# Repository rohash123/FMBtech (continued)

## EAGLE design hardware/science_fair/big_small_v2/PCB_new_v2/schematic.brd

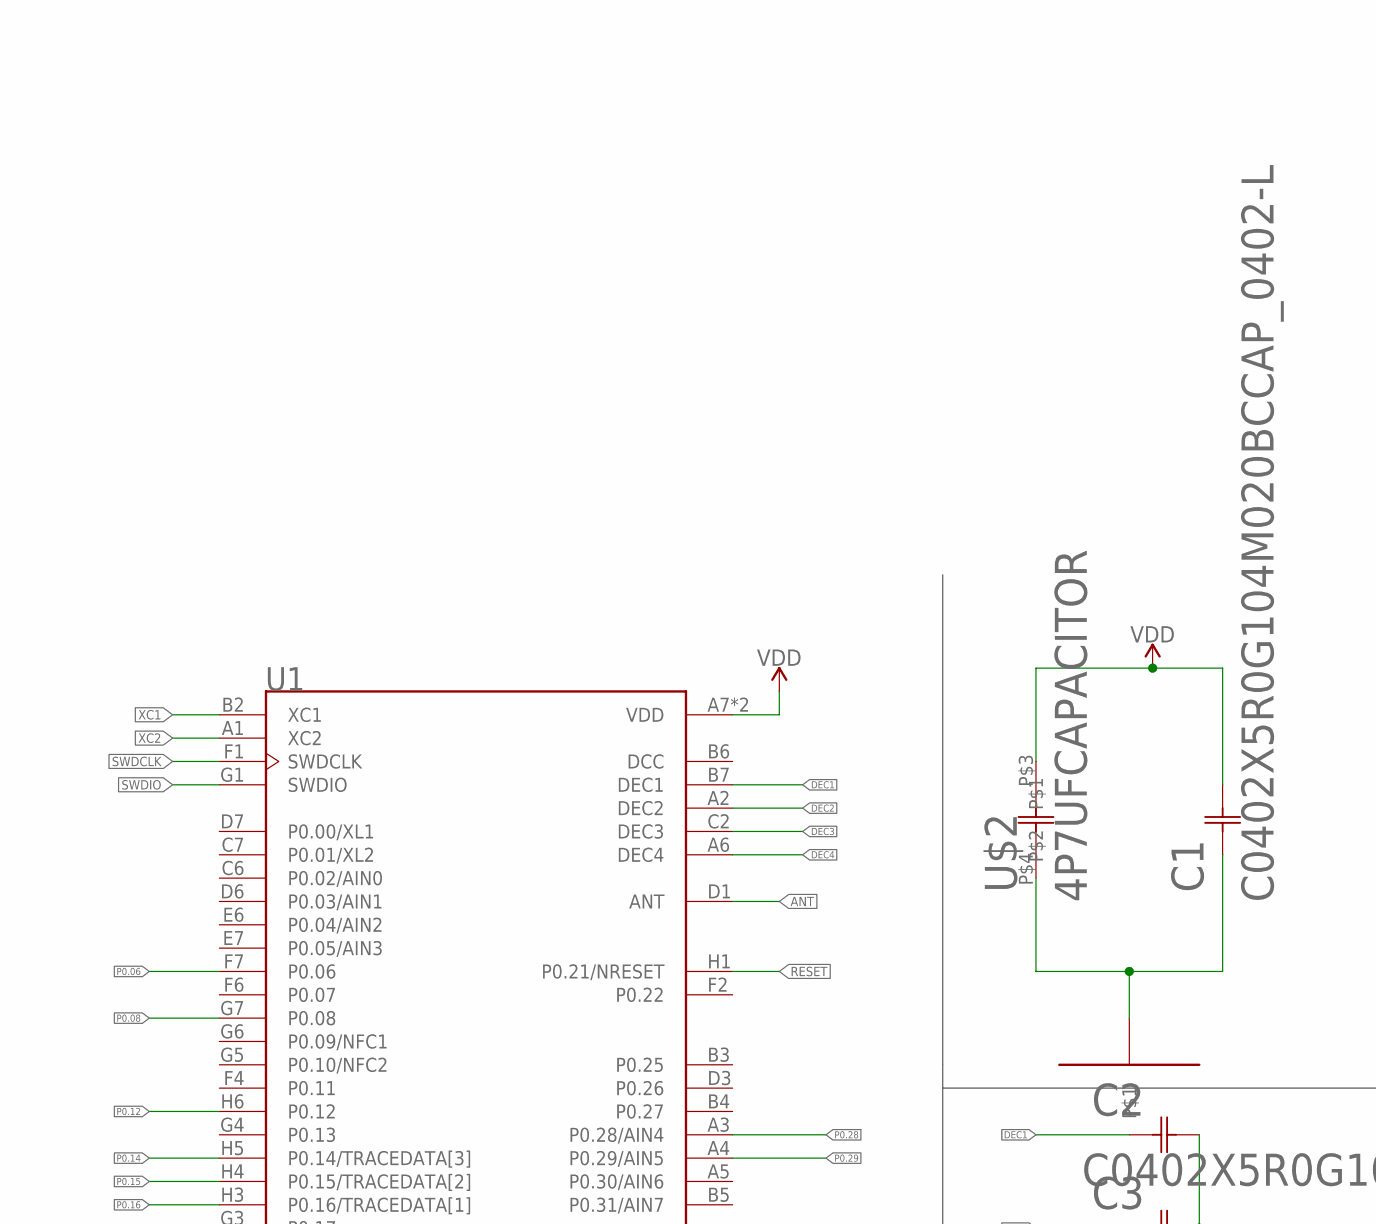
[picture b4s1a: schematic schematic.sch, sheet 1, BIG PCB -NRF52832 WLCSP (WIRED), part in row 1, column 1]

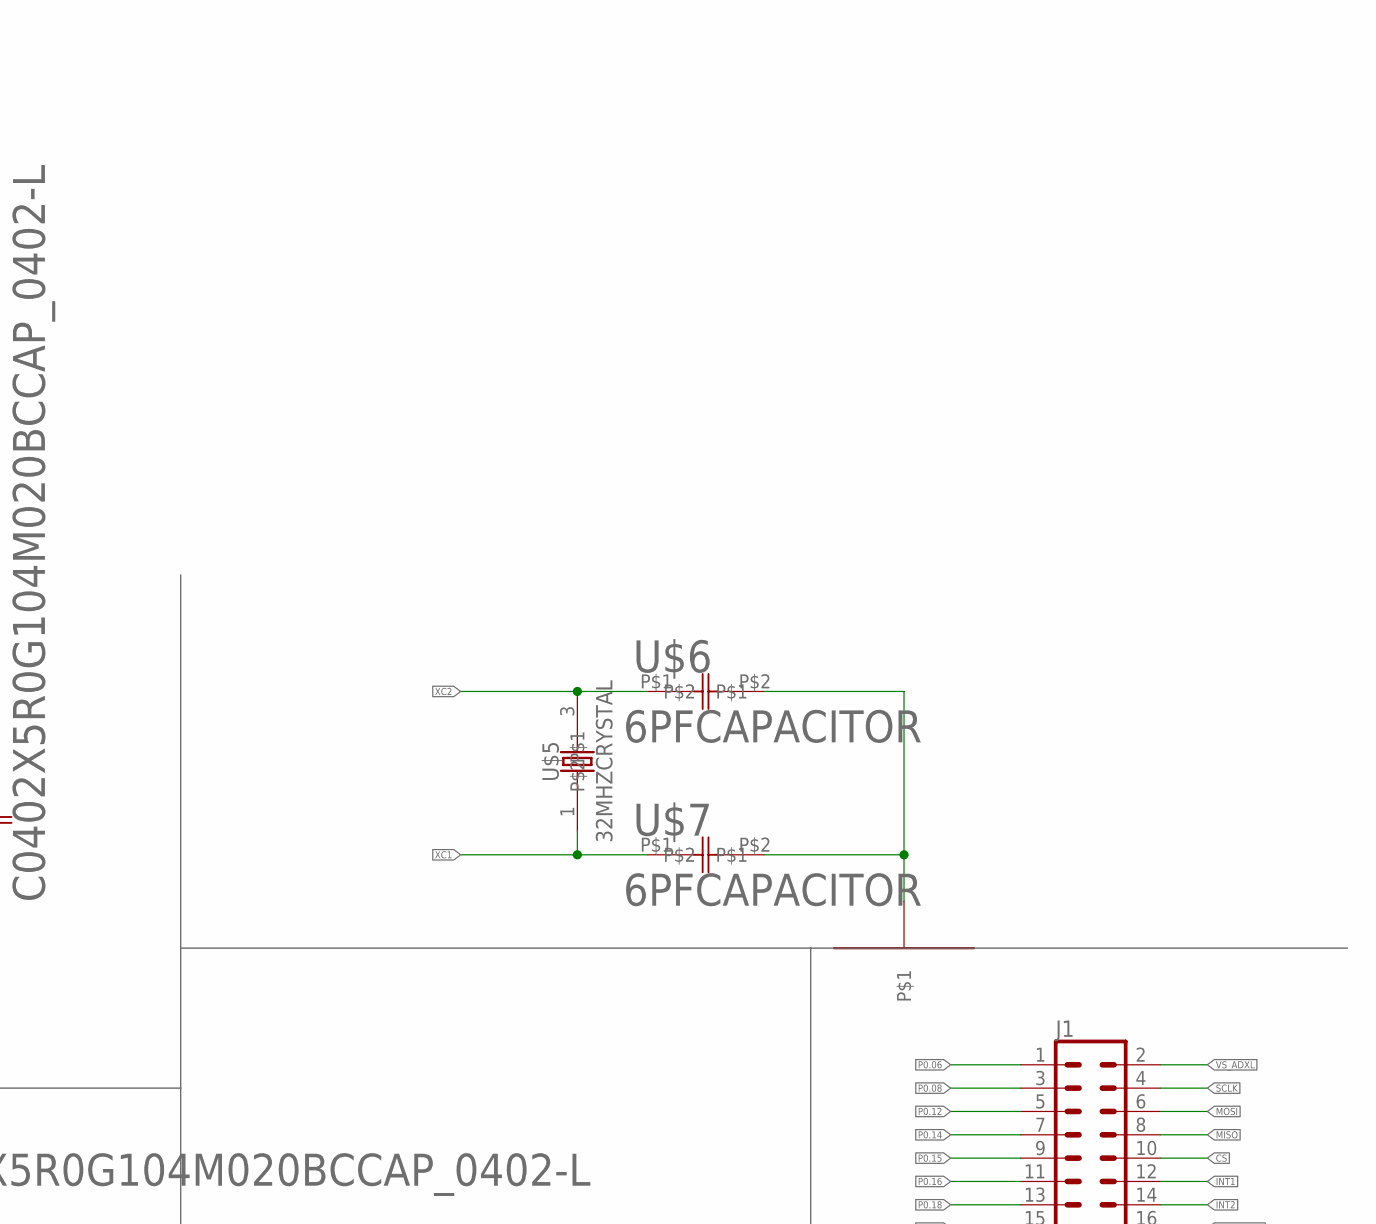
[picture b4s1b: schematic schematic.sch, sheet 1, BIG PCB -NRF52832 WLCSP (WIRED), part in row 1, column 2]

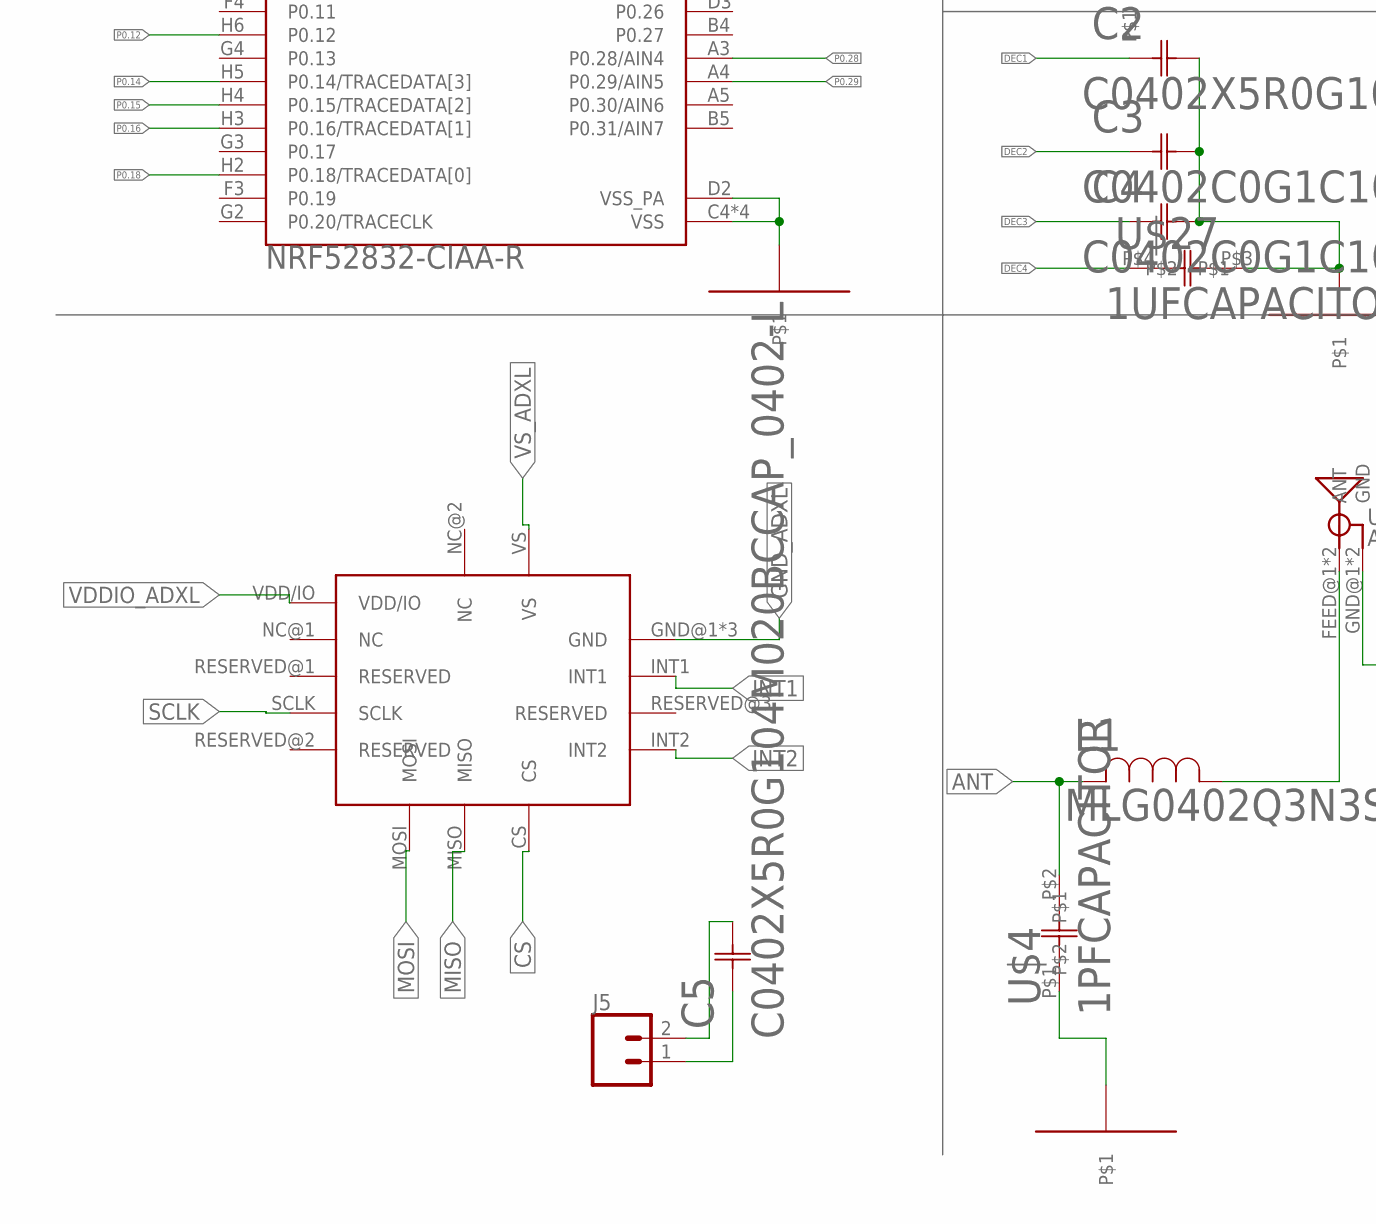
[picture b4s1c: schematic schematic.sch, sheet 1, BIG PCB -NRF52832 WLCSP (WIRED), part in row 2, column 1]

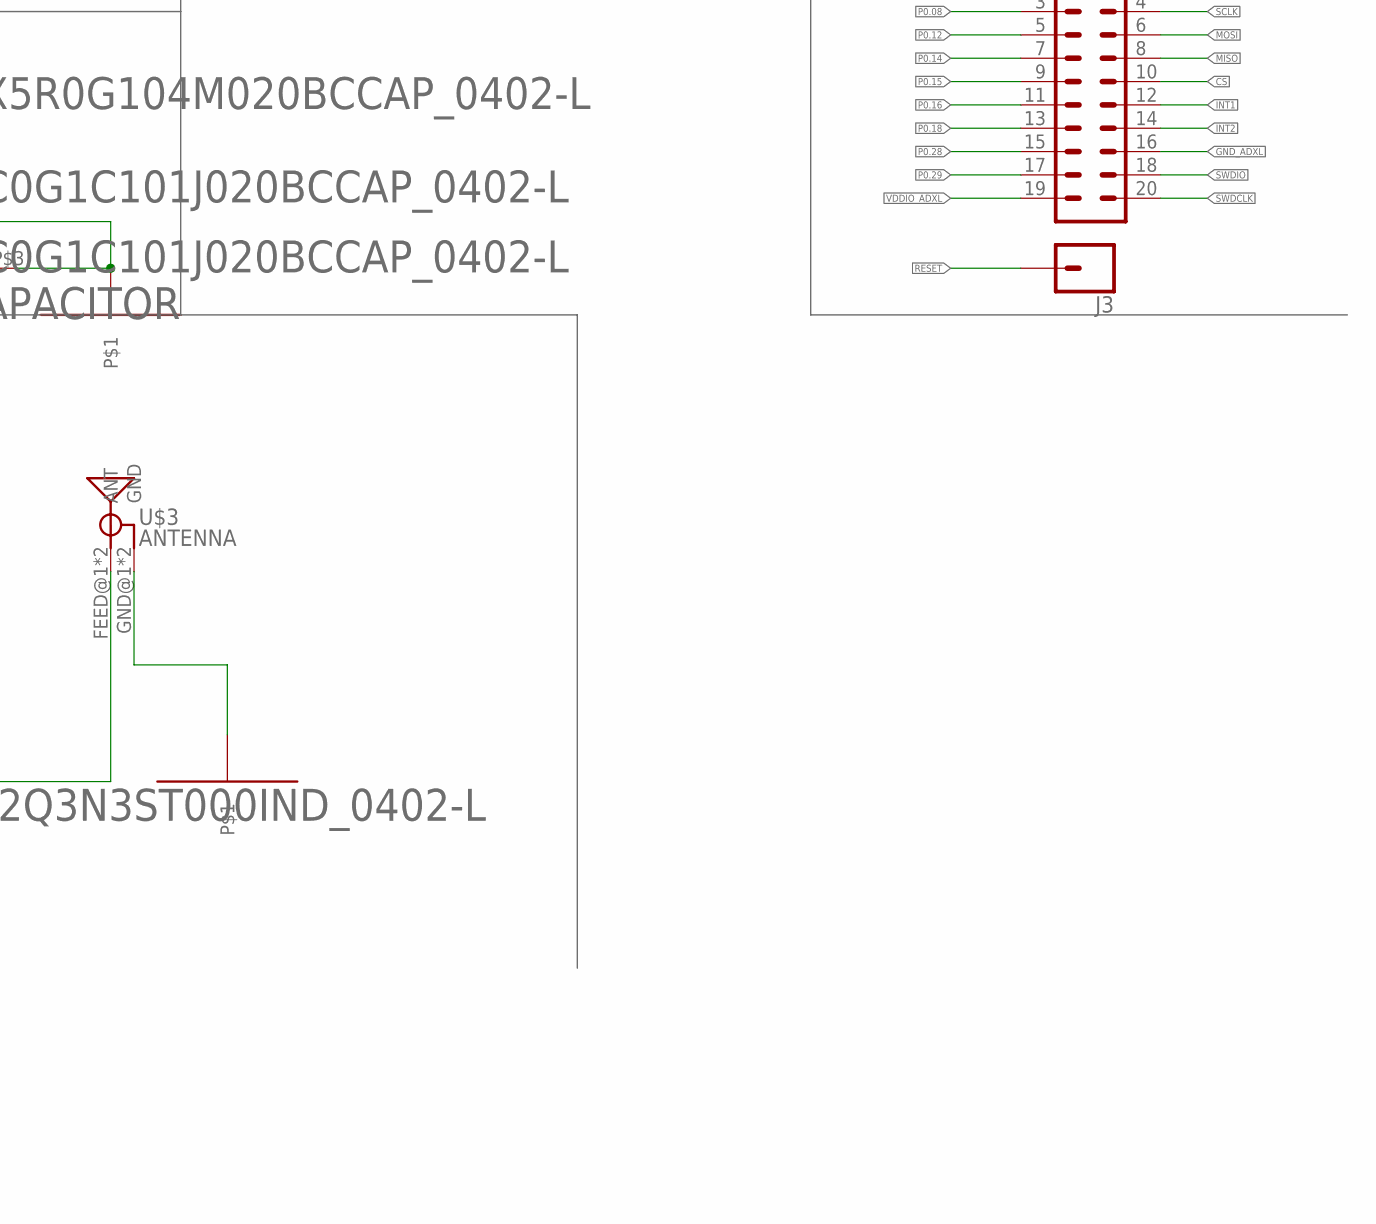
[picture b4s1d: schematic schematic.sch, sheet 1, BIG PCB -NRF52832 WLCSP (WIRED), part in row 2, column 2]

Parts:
C1, C2, C5: C0402X5R0G104M020BCCAP_0402-L; CAP_0402-L
C3, C4: C0402C0G1C101J020BCCAP_0402-L; CAP_0402-L
J1: CONN_10X2; 2X10
J3: CONN_01; 1X01
J5: CONN_02; 1X02
L1: MLG0402Q3N3ST000IND_0402-L; IND_0402-L
U1: NRF52832-CIAA-R; BGA50N40P7X8_300X320X40
U$1: ADXL362; TFLGA-16/3.3MMX3.1MM
U$2: 4P7UFCAPACITOR
U$3: ANTENNA; ANTENNA_FOOTPRINT
U$4: 1PFCAPACITOR
U$5: 32MHZCRYSTAL
U$6, U$7: 6PFCAPACITOR
U$27: 1UFCAPACITOR

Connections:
ANT: L1.2, U1.D1 (ANT), U$4.P$2
CS: J1.10, U$1.CS
DCC: U1.B6 (DCC)
DEC1: C2.1 (11), U1.B7 (DEC1)
DEC2: C3.1 (11), U1.A2 (DEC2)
DEC3: C4.1 (11), U1.C2 (DEC3)
DEC4: U1.A6 (DEC4), U$27.P$4
GND_ADXL: J1.16, U$1.GND@1 (GND), U$1.GND@2 (GND), U$1.GND@3 (GND)
INT1: J1.12, U$1.INT1
INT2: J1.14, U$1.INT2
MISO: J1.8, U$1.MISO
MOSI: J1.6, U$1.MOSI
unnamed: L1.1, U$3.FEED@1 (ANT), U$3.FEED@2 (ANT)
unnamed: C5.2 (22), J5.2
unnamed: C5.1 (11), J5.1
P0.06: J1.1, U1.F7 (P0.06)
P0.08: J1.3, U1.G7 (P0.08)
P0.12: J1.5, U1.H6 (P0.12)
P0.14: J1.7, U1.H5 (P0.14/TRACEDATA[3])
P0.15: J1.9, U1.H4 (P0.15/TRACEDATA[2])
P0.16: J1.11, U1.H3 (P0.16/TRACEDATA[1])
P0.18: J1.13, U1.H2 (P0.18/TRACEDATA[0])
P0.28: J1.15, U1.A3 (P0.28/AIN4)
P0.29: J1.17, U1.A4 (P0.29/AIN5)
P$1: C1.1 (11), C2.2 (22), C3.2 (22), C4.2 (22), U1.C4 (VSS), U1.C5 (VSS), U1.D2 (VSS_PA), U1.E3 (VSS), U1.F5 (VSS), U$2.P$4, U$6.P$2, U$7.P$2, U$27.P$3
RESET: J3.1, U1.H1 (P0.21/NRESET)
SCLK: J1.4, U$1.SCLK
SWDCLK: J1.20, U1.F1 (SWDCLK)
SWDIO: J1.18, U1.G1 (SWDIO)
VDD: C1.2 (22), U1.A7 (VDD), U1.H7 (VDD), U$2.P$3
VDDIO_ADXL: J1.19, U$1.VDD/IO
VSS_PA: U$3.GND@1 (GND), U$3.GND@2 (GND), U$4.P$1
VS_ADXL: J1.2, U$1.VS
XC1: U1.B2 (XC1), U$5.1, U$7.P$1
XC2: U1.A1 (XC2), U$5.3, U$6.P$1
